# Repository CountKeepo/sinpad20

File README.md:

# SINPAD20

## This is my Saatanan Iso Nappi macroPAD with 20 keys, or SINPAD20 for short. 

It is a VIAL-firmware based macropad with a CCCP Missile button (KE-011) as a quirky huge enter button. 
The case is designed and made by [Migii](https://github.com/mkylama) and will most definitely not flip over when you press the huge red button.

**Fun facts:**
- The infamous AZ-5 scram button, which caused the disaster in Chernobyl, was a KE-011 button
- After the accident, starting from 1987, all RBMK reactors had their AZ-5 buttons replaced with a switch
  - The reason for this was that the push-button was prone to multiple inputs.
  - In Chernobyls case, the button press had actually registered twice.

## PCB components list:
- 1 x Atmega32u4 based Pro Micro
- 19 x Cherry MX spec switches of your choice + keycaps
- 1 x CCCP Missile button (KE-011 button, check Ebay etc.)
- 20 x Throughhole 1N4148 diodes or 0805 SMD diodes
- 2 x pieces of electrical wire for hooking up the big ass button to the PCB
- 1 x PCB-mounted 2U stabilizer

## Case - Designed by [Migii](https://github.com/mkylama)
You can find the case files in the [Case-files folder.](https://github.com/CountKeepo/sinpad20/tree/main/Case-files)

### Hardware needed for case build

- 3D-printed material of your choice

- 8 x M2 Heat inserts, 3 mm tall

- 8 x M2x5 countersunk screws, aka 5 mm tall

## Firmware
You can find a premade VIAL compatible firmware file in the [Firmware folder.](https://github.com/CountKeepo/sinpad20/tree/main/Firmware)

## Ordering PCB's
You can find premade gerbers in the [Gerbers folder.](https://github.com/CountKeepo/SIN-pad/tree/main/Sinpad%20Gerbers)  

Otherwise you can use the KiCad files to make your own gerbers.

I ordered my PCB's from ALLPCB and they turned out okay. I cannot guarantee other that other manufacturers will do a good job. 

## Pictures of project:

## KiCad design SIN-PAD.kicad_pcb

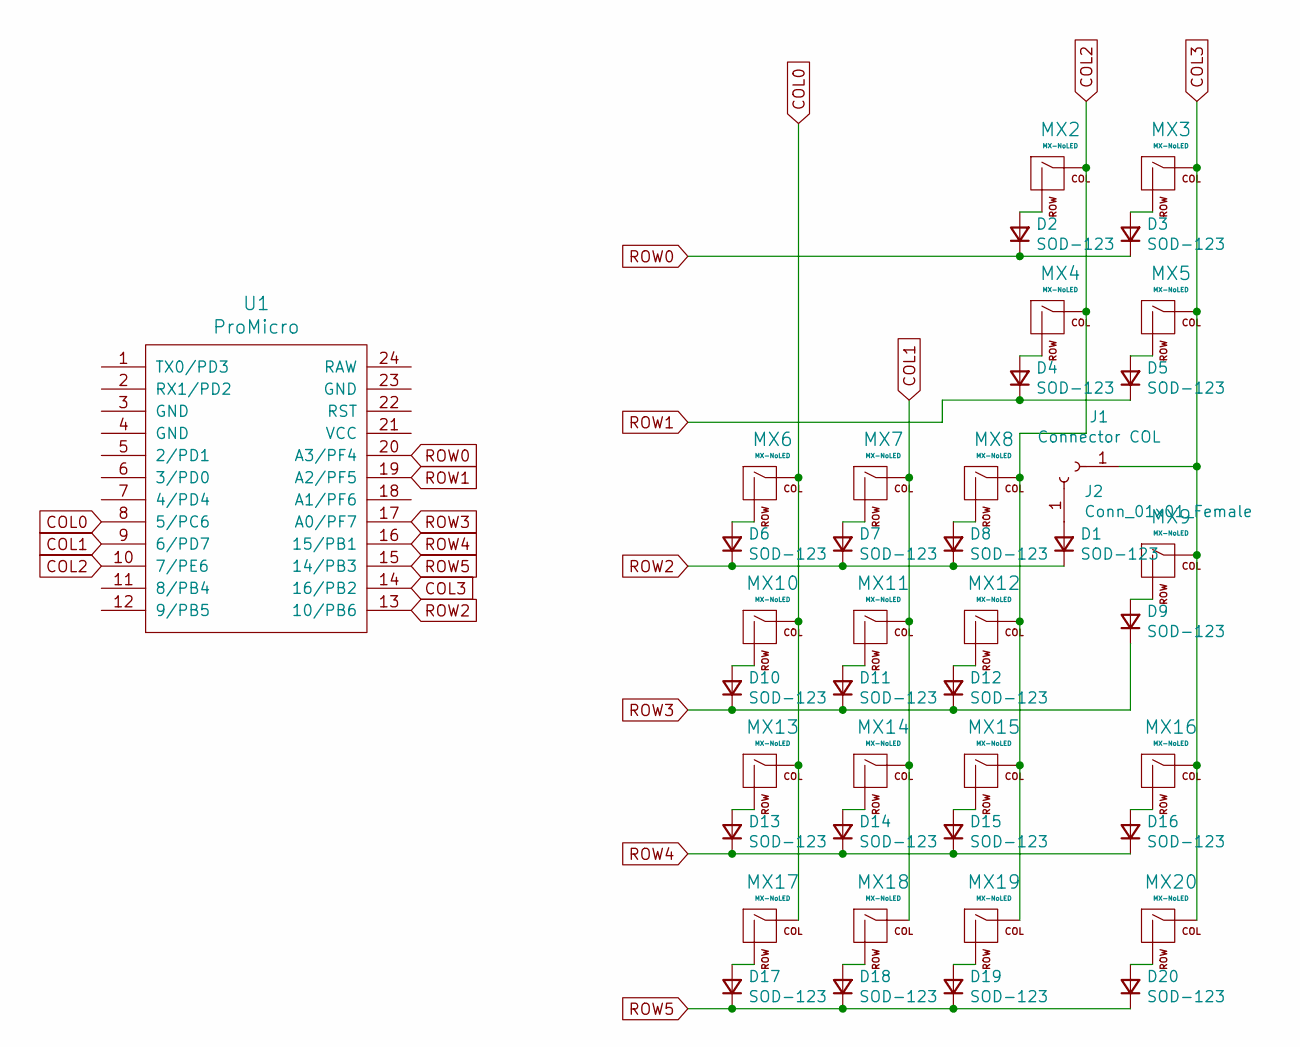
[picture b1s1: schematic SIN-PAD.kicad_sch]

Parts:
D1, D2, D3, D4, D5, D6, D7, D8, D9, D10, D11, D12, D13, D14, D15, D16, D17, D18, D19, D20: SOD-123; Diode-Hybrid-Back
J1: Connector COL; SolderWire-0.5sqmm_1x01_D0.9mm_OD2.3mm
J2: Conn_01x01_Female; SolderWire-0.5sqmm_1x01_D0.9mm_OD2.3mm
MX2, MX3, MX4, MX5, MX6, MX7, MX8, MX10, MX11, MX12, MX13, MX14, MX15, MX16, MX17, MX18, MX19, MX20: MX-NoLED; MXOnly-1U-NoLED
MX9: MX-NoLED; MXOnly-2U-NoLED
U1: ProMicro; ArduinoProMicro

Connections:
COL0: MX6.1 (COL), MX10.1 (COL), MX13.1 (COL), MX17.1 (COL), U1.8 (5/PC6)
COL1: MX7.1 (COL), MX11.1 (COL), MX14.1 (COL), MX18.1 (COL), U1.9 (6/PD7)
COL2: MX2.1 (COL), MX4.1 (COL), MX8.1 (COL), MX12.1 (COL), MX15.1 (COL), MX19.1 (COL), U1.10 (7/PE6)
COL3: J1.1, MX3.1 (COL), MX5.1 (COL), MX9.1 (COL), MX16.1 (COL), MX20.1 (COL), U1.14 (16/PB2)
unnamed: D1.2 (A), J2.1
unnamed: D2.2 (A), MX2.2 (ROW)
unnamed: D3.2 (A), MX3.2 (ROW)
unnamed: D4.2 (A), MX4.2 (ROW)
unnamed: D5.2 (A), MX5.2 (ROW)
unnamed: D6.2 (A), MX6.2 (ROW)
unnamed: D7.2 (A), MX7.2 (ROW)
unnamed: D8.2 (A), MX8.2 (ROW)
unnamed: D9.2 (A), MX9.2 (ROW)
unnamed: D10.2 (A), MX10.2 (ROW)
unnamed: D11.2 (A), MX11.2 (ROW)
unnamed: D12.2 (A), MX12.2 (ROW)
unnamed: D13.2 (A), MX13.2 (ROW)
unnamed: D14.2 (A), MX14.2 (ROW)
unnamed: D15.2 (A), MX15.2 (ROW)
unnamed: D16.2 (A), MX16.2 (ROW)
unnamed: D17.2 (A), MX17.2 (ROW)
unnamed: D18.2 (A), MX18.2 (ROW)
unnamed: D19.2 (A), MX19.2 (ROW)
unnamed: D20.2 (A), MX20.2 (ROW)
ROW0: D2.1 (K), D3.1 (K), U1.20 (A3/PF4)
ROW1: D4.1 (K), D5.1 (K), U1.19 (A2/PF5)
ROW2: D1.1 (K), D6.1 (K), D7.1 (K), D8.1 (K), U1.13 (10/PB6)
ROW3: D9.1 (K), D10.1 (K), D11.1 (K), D12.1 (K), U1.17 (A0/PF7)
ROW4: D13.1 (K), D14.1 (K), D15.1 (K), D16.1 (K), U1.16 (15/PB1)
ROW5: D17.1 (K), D18.1 (K), D19.1 (K), D20.1 (K), U1.15 (14/PB3)

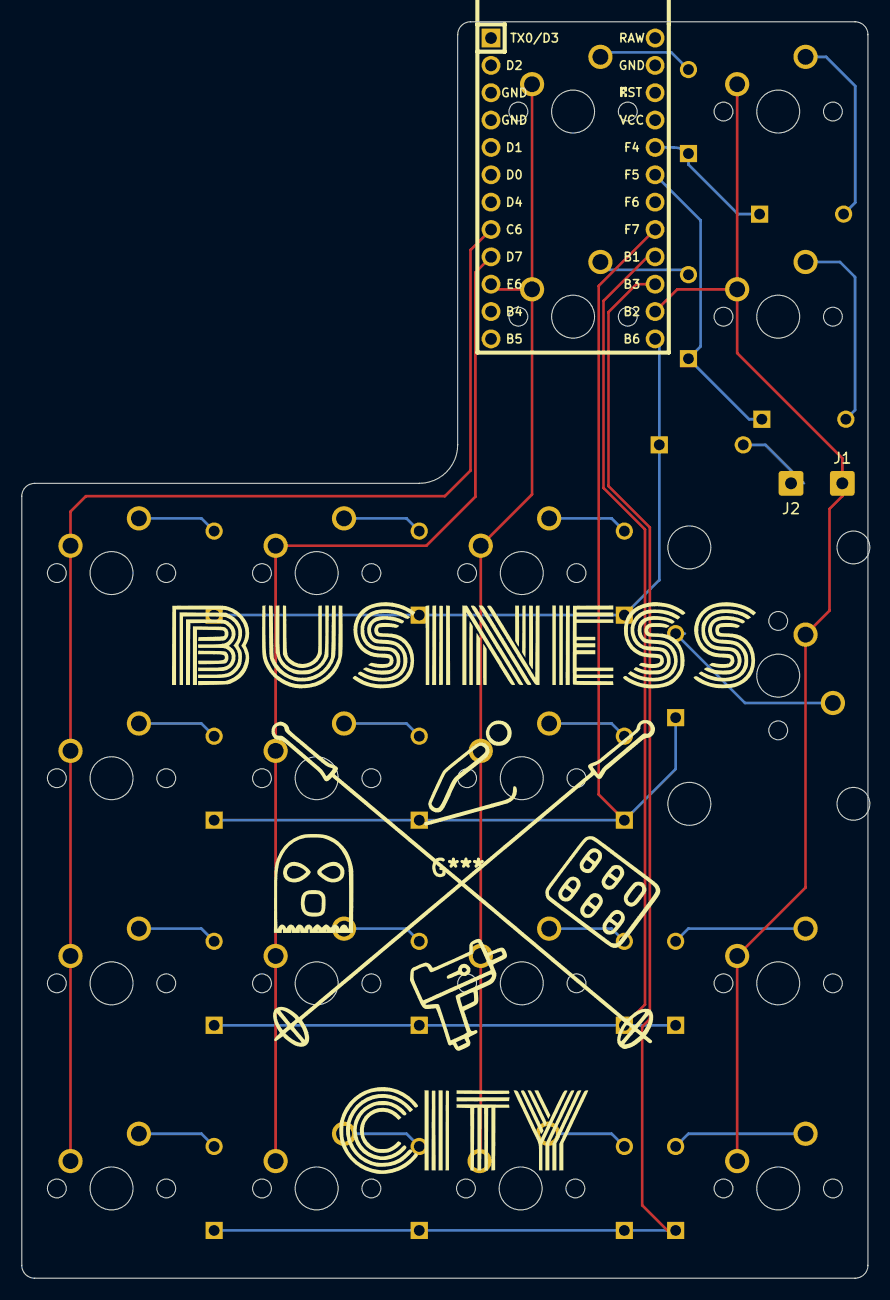
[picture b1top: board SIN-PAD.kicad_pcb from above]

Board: 2 copper layers, 78.6 x 116.7 mm, 43 parts (1 on the bottom side), 30 nets.

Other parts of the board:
  : LOGO; pikkunimmari

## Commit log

2021-10-04 Pelkät projufilut
2021-10-04 Add submodules
2021-10-04 Uus committaus
2021-10-04 Uusia edustuksia
2021-10-04 Kytkimet lätkitty tiskiin
2021-10-04 Big brain commit 23:36
2021-10-04 Nyt alkaa muodostuu
2021-10-04 Muutoxia
2022-05-14 Muutamii muutoksia
2022-05-14 Poistettu kamaa
2022-07-19 Rename sinpad20_vial.hex to Firmware/sinpad20_vial.hex
2022-07-19 QMK + VIAL files for compiling
2024-01-26 Added case files finally
    Blame it on procrastination or forgetting to ask for it but I finally remembered to add the case files.
